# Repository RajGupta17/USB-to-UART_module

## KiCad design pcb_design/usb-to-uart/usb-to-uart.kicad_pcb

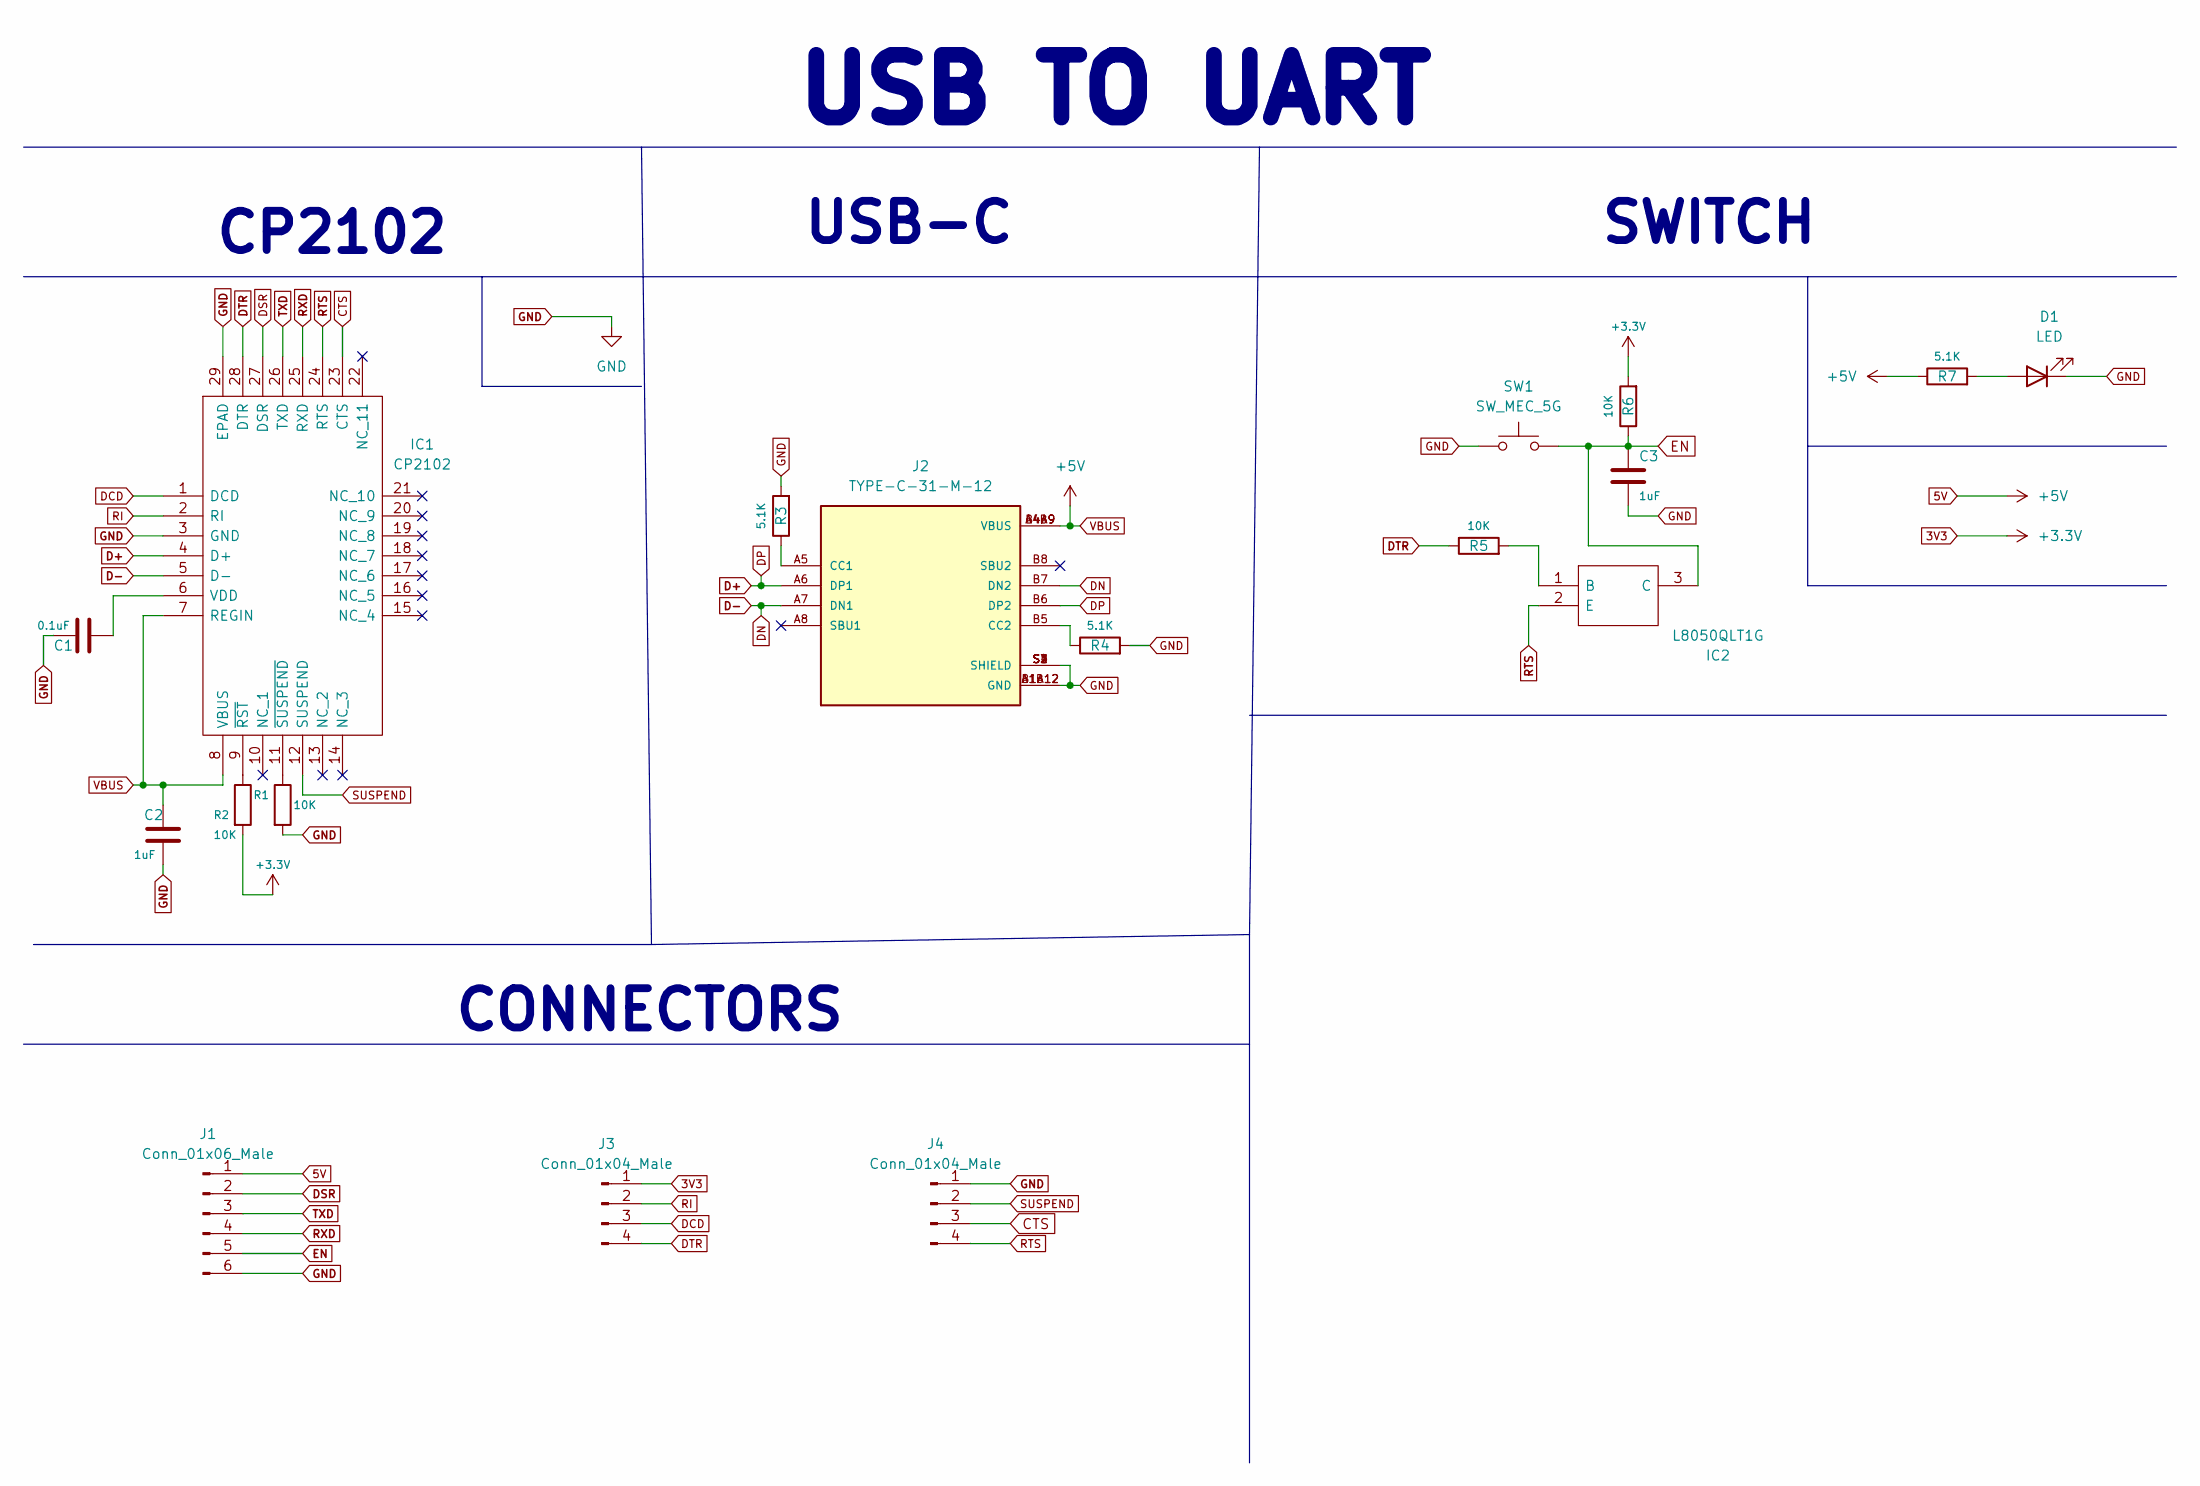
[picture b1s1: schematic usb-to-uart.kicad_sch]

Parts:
C1: 0.1uF; C_0603_1608Metric
C2, C3: 1uF; C_0603_1608Metric
D1: LED; LED_0603_1608Metric
IC1: CP2102; QFN50P500X500X100-29N; Manufacturer_Part_Number CP2102; Mouser Part Number 634-CP2102
IC2: L8050QLT1G; Manufacturer_Part_Number L8050QLT1G
J1: Conn_01x06_Male; TE_825433-6
J2: TYPE-C-31-M-12; HRO_TYPE-C-31-M-12; PARTREV A
J3, J4: Conn_01x04_Male; 61300411121
R1, R2, R5, R6: 10K; LED_0603_1608Metric
R3, R4, R7: 5.1K; LED_0603_1608Metric
SW1: SW_MEC_5G; SW_TL3305AF260QG

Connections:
3V3: J3.1, R2.2, R6.2
5V: C2.1, IC1.7 (REGIN), IC1.8 (VBUS), J1.1, J2.A4B9 (VBUS), J2.B4A9 (VBUS), R7.1
CTS: IC1.23 (CTS), J4.3
D+: IC1.4 (D+), J2.A6 (DP1), J2.B6 (DP2)
D-: IC1.5 (D-), J2.A7 (DN1), J2.B7 (DN2)
DCD: IC1.1 (DCD), J3.3
DSR: IC1.27 (DSR), J1.2
DTR: IC1.28 (DTR), J3.4, R5.1
EN: C3.1, IC2.3 (C), J1.5, R6.1, SW1.3 (B), SW1.4 (B)
GND: C1.1, C2.2, C3.2, D1.1 (K), IC1.3 (GND), IC1.29 (EPAD), J1.6, J2.A1B12 (GND), J2.B1A12 (GND), J2.S1 (SHIELD), J2.S2 (SHIELD), J2.S3 (SHIELD), J2.S4 (SHIELD), J4.1, R1.2, R3.2, R4.2, SW1.1 (A), SW1.2 (A)
unnamed: C1.2, IC1.6 (VDD)
unnamed: D1.2 (A), R7.2
unnamed: IC1.9 (~RST), R2.1
unnamed: IC1.11 (~SUSPEND), R1.1
unnamed: IC2.1 (B), R5.2
unnamed: J2.A5 (CC1), R3.1
unnamed: J2.B5 (CC2), R4.1
RI: IC1.2 (RI), J3.2
RTS: IC1.24 (RTS), IC2.2 (E), J4.4
RXD: IC1.25 (RXD), J1.4
SUSPEND: IC1.12 (SUSPEND), J4.2
TXD: IC1.26 (TXD), J1.3

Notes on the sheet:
SWITCH
CONNECTORS
CP2102
USB TO UART
USB-C

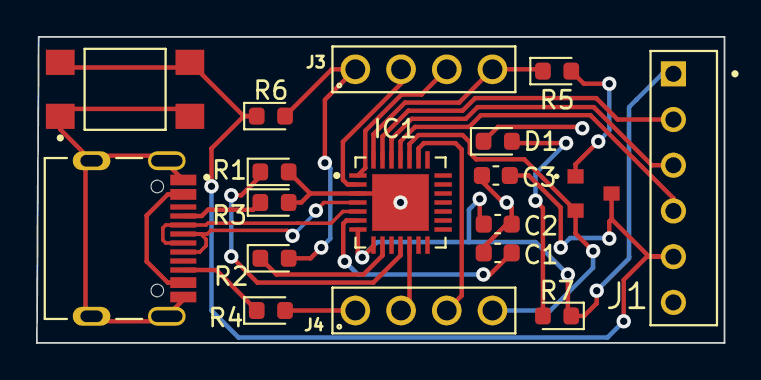
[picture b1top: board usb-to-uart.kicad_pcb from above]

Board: 2 copper layers, 38.2 x 17.0 mm, 18 parts (0 on the bottom side), 22 nets.

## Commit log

2023-01-25 added pcb_design folder
2023-01-26 completed schematic design
2023-01-27 footprint assignment done
2023-01-31 routing 1 completed
2023-02-05 PCB Completed
